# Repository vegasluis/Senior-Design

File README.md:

# Senior-Design

# Problem Identified
Pedestrian fatality rate is three times higher at night. Per the Traffic Safety Facts
(2012 Data), 70% of the pedestrians are killed in the nighttime (6PM – 5:59AM).
A driver can only avoid an accident if he/she sees the pedestrian relatively far
ahead. Headlights only let the driver see about 350 feet ahead.

# Current Solutions
The closest solution in the market is the innovative design Audi has incorporated
to their car model; the Audi A4 is more for personal use rather than a pubic
design. Crosswalk lighting on the street is available to light up sections of the
crosswalk once the light is pressed. Overhead flashing lights, like the Hawk
System, are also used with a set timer to warn drivers that pedestrians are trying
to cross. One tested solution is setting two posts on both sides of the street,
such that once a pedestrian presses a button, the lights turn on to illuminate the
crosswalk.

# Team’s Solution
The Pedestrian Lighting Guidance System is a more efficient way to solve
pedestrian fatalities due to poor visibility at night. The system will be very userfriendly. Pedestrians would not have to do anything different than they usually
do when crossing the street at night, because the pedestrian detection software
will control the spotlight whenever someone triggers it. The system will run
autonomously. The main detail of the
PLGS is its ability to view any object
crossing in the intersection using the
OpenCV libraries. The cameras process
the incoming images and relay the
position to the microprocessors that
control the motor servos, which rotate
180 degrees and will be able to move
the focused spotlights from one side of
the crosswalk to the other. The device
we are trying to create is optimized
more for industrial use, not for
consumer use. It does not require any
sort of reconstruction or modification
on the road.

# Youtube URL

https://www.youtube.com/watch?v=EUFnc7yAI7A

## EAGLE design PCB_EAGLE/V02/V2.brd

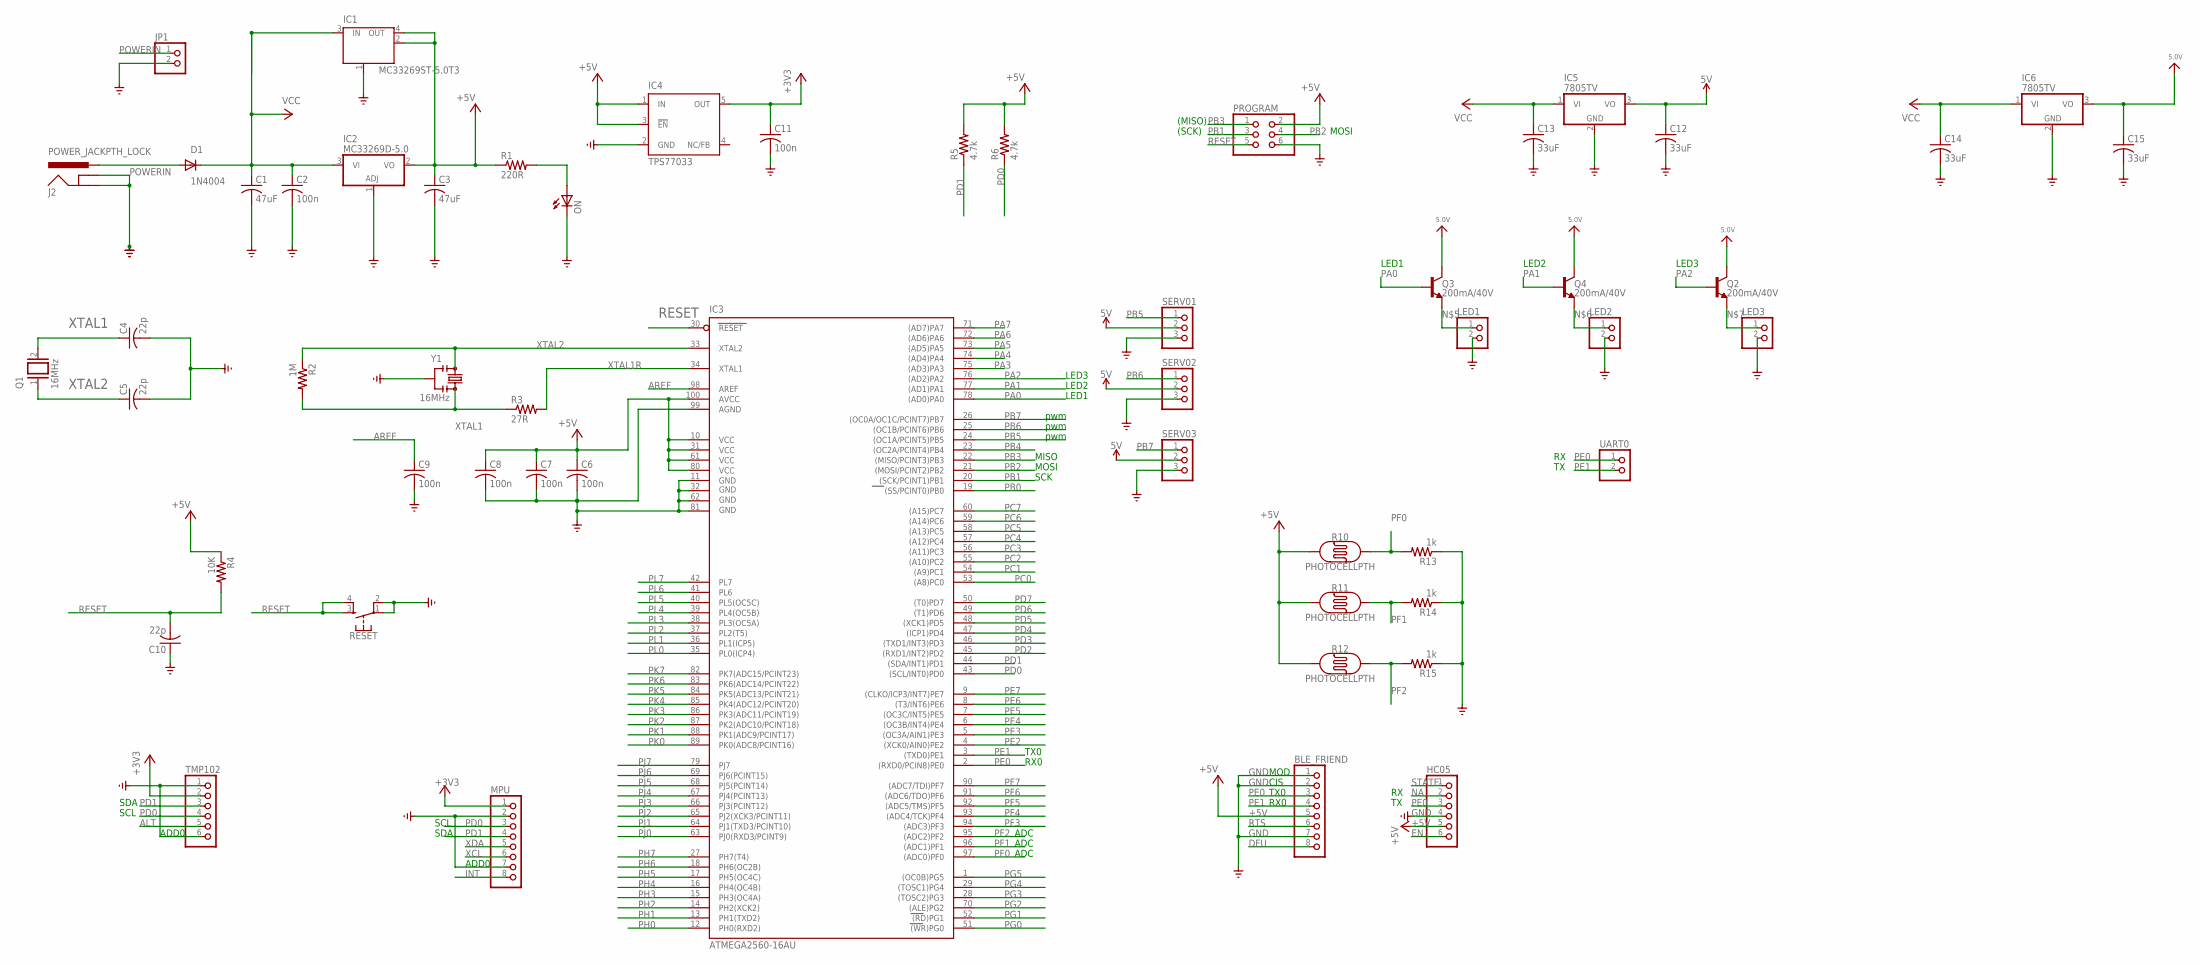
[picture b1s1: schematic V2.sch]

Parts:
BLE_FRIEND: PINHD-1X8; 1X08
C1, C3: 47uF; C025-024X044
C2, C6, C7, C8, C9, C11: 100n; C025-024X044
C4, C5, C10: 22p; C025-024X044
C12, C13, C14, C15: 33uF; C025-024X044
D1: 1N4004; DO41-10
HC05: PINHD-1X6; 1X06
IC1: MC33269ST-5.0T3; SOT223
IC2: MC33269D-5.0; DPACK
IC3: ATMEGA2560-16AU; TQFP100
IC4: TPS77033; SOT23-DBV
IC5, IC6: 7805TV; TO220V
J2: POWER_JACKPTH_LOCK; POWER_JACK_PTH_LOCK
JP1: PINHD-1X2; 1X02
LED1, LED2, LED3: PINHD-1X2; 1X02
MPU: PINHD-1X8; 1X08
ON: LED3MM
PROGRAM: PINHD-2X3; 2X03
Q1: 16MHz; QS
Q2, Q3, Q4: 200mA/40V; TO-92
R1: 220R; 0204V
R2: 1M; 0204V
R3: 27R; 0204V
R4: 10K; 0204V
R5, R6: 4.7k; 0204V
R10, R11, R12: PHOTOCELLPTH; PHOTOCELL
R13, R14, R15: 1k; 0204V
RESET: MOMENTARY-SWITCH-SPST-2-SMD-5.2MM; TACTILE_SWITCH_SMD_5.2MM
SERV01, SERV02, SERV03: PINHD-1X3; 1X03
TMP102: PINHD-1X6; 1X06
UART0: PINHD-1X2; 1X02
Y1: 16MHz; RESONATOR-SMD-3.2X1.3

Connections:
5.0V: C15.1, IC6.3 (VO), Q2.3 (C), Q3.3 (C), Q4.3 (C)
5V: C12.1, IC5.3 (VO), SERV01.2, SERV02.2, SERV03.2
+3V3: C11.1, IC4.5 (OUT), MPU.1, TMP102.2
+5V: BLE_FRIEND.5, C3.1, C6.1, C7.1, C8.1, HC05.5, IC1.2 (OUT), IC1.4 (OUT), IC2.2 (VO), IC3.10 (VCC), IC3.31 (VCC1), IC3.61 (VCC2), IC3.80 (VCC3), IC3.100 (AVCC), IC4.1 (IN), IC4.3 (!EN), PROGRAM.2, R1.1, R4.1, R5.2, R6.2, R10.1, R11.1, R12.1
ALT: TMP102.5
AREF: C9.1, IC3.98 (AREF)
DFU: BLE_FRIEND.8
EN: HC05.6
GND: BLE_FRIEND.1, BLE_FRIEND.2, BLE_FRIEND.7, C1.2, C2.2, C3.2, C4.2, C5.2, C6.2, C7.2, C8.2, C9.2, C10.1, C11.2, C12.2, C13.2, C14.2, C15.2, HC05.4, IC1.1 (GND/ADJ), IC2.1 (ADJ), IC3.11 (GND), IC3.32 (GND1), IC3.62 (GND2), IC3.81 (GND3), IC3.99 (AGND), IC4.2 (GND), IC5.2 (GND), IC6.2 (GND), J2.GND, J2.GNDBREAK, JP1.2, LED1.2, LED2.2, LED3.2, MPU.2, MPU.7, ON.K (C), PROGRAM.6, R13.1, R14.1, R15.1, RESET.1, RESET.2, SERV01.3, SERV02.3, SERV03.3, TMP102.1, TMP102.6, Y1.2
INT: MPU.8
unnamed: ON.A, R1.2
unnamed: LED1.1, Q3.1 (E)
unnamed: LED2.1, Q4.1 (E)
unnamed: LED3.1, Q2.1 (E)
NA: HC05.2
PA0: IC3.78 ((AD0)PA0), Q3.2 (B)
PA1: IC3.77 ((AD1)PA1), Q4.2 (B)
PA2: IC3.76 ((AD2)PA2), Q2.2 (B)
PA3: IC3.75 ((AD3)PA3)
PA4: IC3.74 ((AD4)PA4)
PA5: IC3.73 ((AD5)PA5)
PA6: IC3.72 ((AD6)PA6)
PA7: IC3.71 ((AD7)PA7)
PB0: IC3.19 ((SS/PCINT0)PB0)
PB1: IC3.20 ((SCK/PCINT1)PB1), PROGRAM.3
PB2: IC3.21 ((MOSI/PCINT2)PB2), PROGRAM.4
PB3: IC3.22 ((MISO/PCINT3)PB3), PROGRAM.1
PB4: IC3.23 ((OC2A/PCINT4)PB4)
PB5: IC3.24 ((OC1A/PCINT5)PB5), SERV01.1
PB6: IC3.25 ((OC1B/PCINT6)PB6), SERV02.1
PB7: IC3.26 ((OC0A/OC1C/PCINT7)PB7), SERV03.1
PC0: IC3.53 ((A8)PC0)
PC1: IC3.54 ((A9)PC1)
PC2: IC3.55 ((A10)PC2)
PC3: IC3.56 ((A11)PC3)
PC4: IC3.57 ((A12)PC4)
PC5: IC3.58 ((A13)PC5)
PC6: IC3.59 ((A14)PC6)
PC7: IC3.60 ((A15)PC7)
PD0: IC3.43 ((SCL/INT0)PD0), MPU.3, R6.1, TMP102.4
PD1: IC3.44 ((SDA/INT1)PD1), MPU.4, R5.1, TMP102.3
PD2: IC3.45 ((RXD1/INT2)PD2)
PD3: IC3.46 ((TXD1/INT3)PD3)
PD4: IC3.47 ((ICP1)PD4)
PD5: IC3.48 ((XCK1)PD5)
PD6: IC3.49 ((T1)PD6)
PD7: IC3.50 ((T0)PD7)
PE0: BLE_FRIEND.3, HC05.3, IC3.2 ((RXD0/PCIN8)PE0), UART0.1
PE1: BLE_FRIEND.4, IC3.3 ((TXD0)PE1), UART0.2
PE2: IC3.4 ((XCK0/AIN0)PE2)
PE3: IC3.5 ((OC3A/AIN1)PE3)
PE4: IC3.6 ((OC3B/INT4)PE4)
PE5: IC3.7 ((OC3C/INT5)PE5)
PE6: IC3.8 ((T3/INT6)PE6)
PE7: IC3.9 ((CLKO/ICP3/INT7)PE7)
PF0: IC3.97 ((ADC0)PF0), R10.2, R13.2
PF1: IC3.96 ((ADC1)PF1), R11.2, R14.2
PF2: IC3.95 ((ADC2)PF2), R12.2, R15.2
PF3: IC3.94 ((ADC3)PF3)
PF4: IC3.93 ((ADC4/TCK)PF4)
PF5: IC3.92 ((ADC5/TMS)PF5)
PF6: IC3.91 ((ADC6/TDO)PF6)
PF7: IC3.90 ((ADC7/TDI)PF7)
PG0: IC3.51 ((WR)PG0)
PG1: IC3.52 ((RD)PG1)
PG2: IC3.70 ((ALE)PG2)
PG3: IC3.28 ((TOSC2)PG3)
PG4: IC3.29 ((TOSC1)PG4)
PG5: IC3.1 ((OC0B)PG5)
PH0: IC3.12 (PH0(RXD2))
PH1: IC3.13 (PH1(TXD2))
PH2: IC3.14 (PH2(XCK2))
PH3: IC3.15 (PH3(OC4A))
PH4: IC3.16 (PH4(OC4B))
PH5: IC3.17 (PH5(OC4C))
PH6: IC3.18 (PH6(OC2B))
PH7: IC3.27 (PH7(T4))
PJ0: IC3.63 (PJ0(RXD3/PCINT9))
PJ1: IC3.64 (PJ1(TXD3/PCINT10))
PJ2: IC3.65 (PJ2(XCK3/PCINT11))
PJ3: IC3.66 (PJ3(PCINT12))
PJ4: IC3.67 (PJ4(PCINT13))
PJ5: IC3.68 (PJ5(PCINT14))
PJ6: IC3.69 (PJ6(PCINT15))
PJ7: IC3.79 (PJ7)
PK0: IC3.89 (PK0(ADC8/PCINT16))
PK1: IC3.88 (PK1(ADC9/PCINT17))
PK2: IC3.87 (PK2(ADC10/PCINT18))
PK3: IC3.86 (PK3(ADC11/PCINT19))
PK4: IC3.85 (PK4(ADC12/PCINT20))
PK5: IC3.84 (PK5(ADC13/PCINT21))
PK6: IC3.83 (PK6(ADC14/PCINT22))
PK7: IC3.82 (PK7(ADC15/PCINT23))
PL0: IC3.35 (PL0(ICP4))
PL1: IC3.36 (PL1(ICP5))
PL2: IC3.37 (PL2(T5))
PL3: IC3.38 (PL3(OC5A))
PL4: IC3.39 (PL4(OC5B))
PL5: IC3.40 (PL5(OC5C))
PL6: IC3.41 (PL6)
PL7: IC3.42 (PL7)
POWERIN: D1.A, J2.PWR, JP1.1
RESET: C10.2, IC3.30 (RESET), PROGRAM.5, R4.2, RESET.3, RESET.4
RTS: BLE_FRIEND.6
STATE: HC05.1
VCC: C1.1, C2.1, C13.1, C14.1, D1.C, IC1.3 (IN), IC2.3 (VI), IC5.1 (VI), IC6.1 (VI)
XCL: MPU.6
XDA: MPU.5
XTAL1: C4.1, Q1.2, R2.2, R3.1, Y1.3
XTAL1R: IC3.34 (XTAL1), R3.2
XTAL2: C5.1, IC3.33 (XTAL2), Q1.1, R2.1, Y1.1

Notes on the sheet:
pwm
ADD0
ADC
(MISO)
(SCK)
MOSI
MISO
SCK
TX0
RX0
SDA
SCL
MOD
CIS
LED1
LED2
LED3

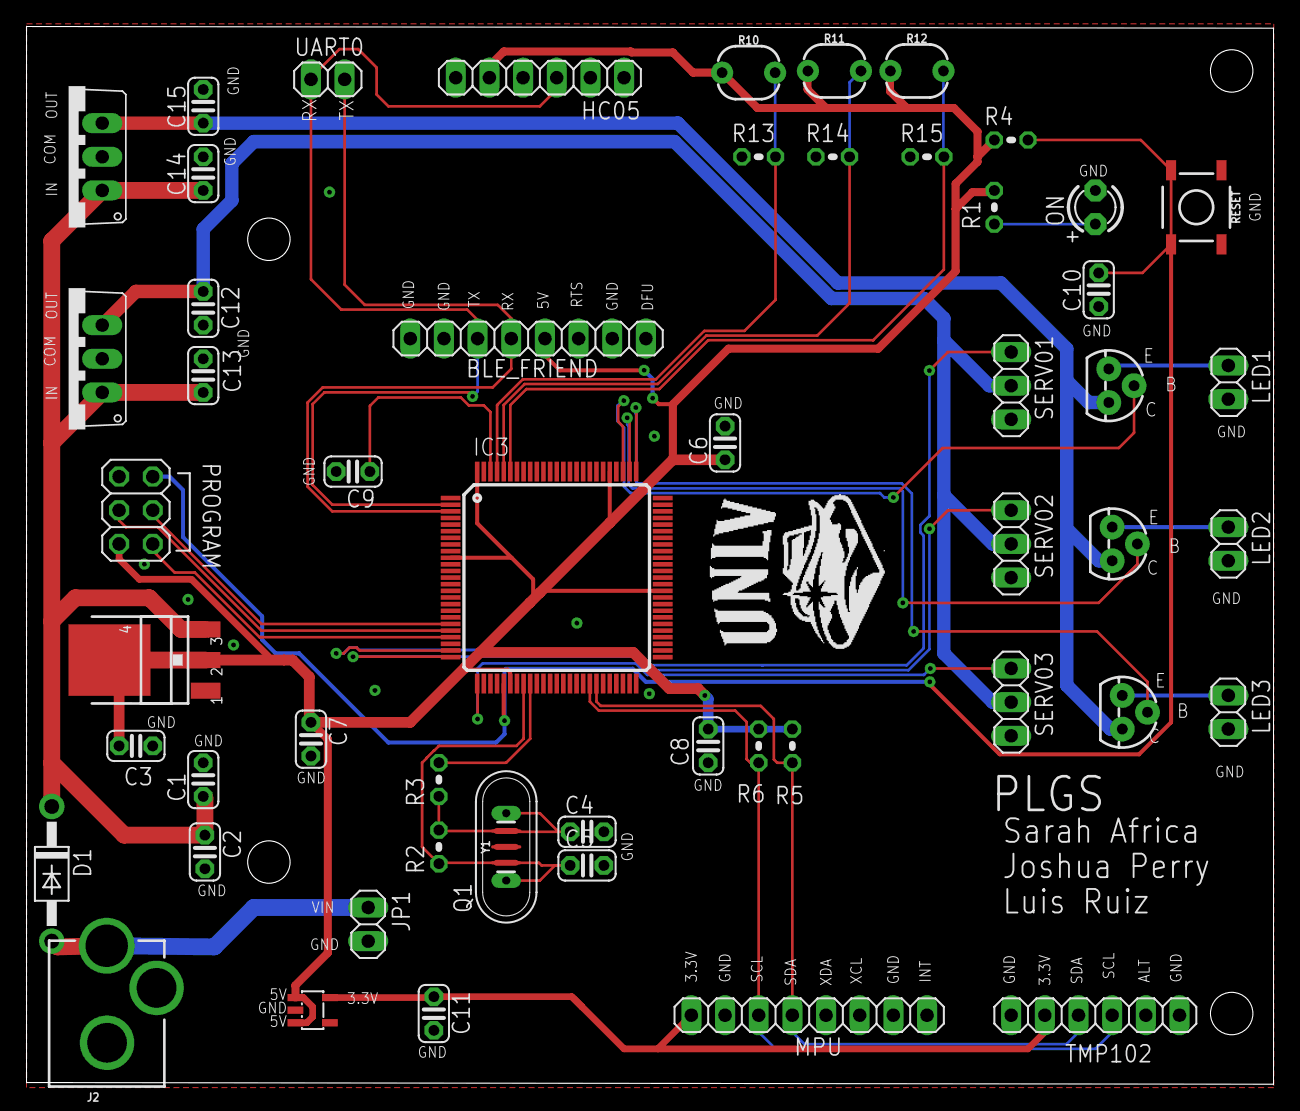
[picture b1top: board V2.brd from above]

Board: 2 copper layers, 94.1 x 79.8 mm, 55 parts (0 on the bottom side), 32 nets.

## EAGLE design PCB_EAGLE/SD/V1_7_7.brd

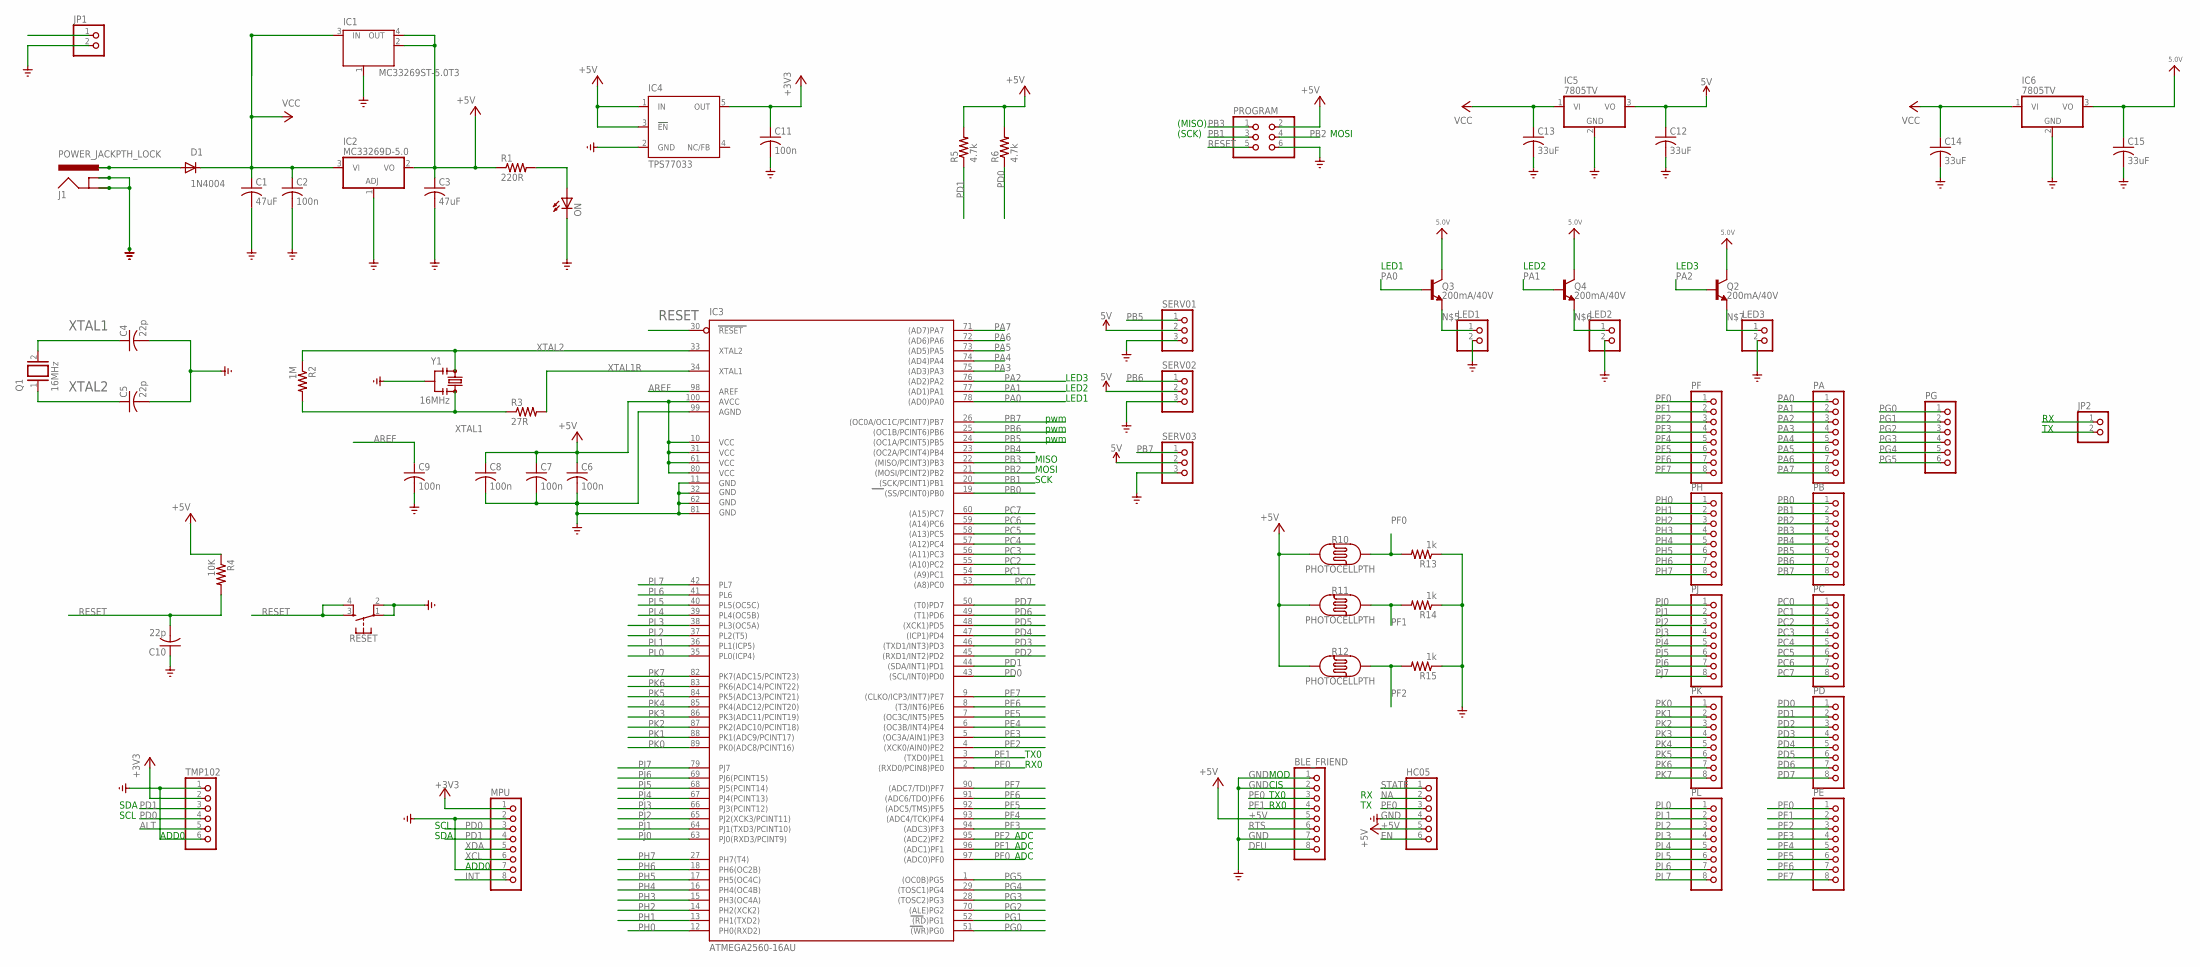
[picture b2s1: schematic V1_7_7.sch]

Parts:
BLE_FRIEND: PINHD-1X8; 1X08
C1, C3: 47uF; C025-024X044
C2, C6, C7, C8, C9, C11: 100n; C025-024X044
C4, C5, C10: 22p; C025-024X044
C12, C13, C14, C15: 33uF; C025-024X044
D1: 1N4004; DO41-10
HC05: PINHD-1X6; 1X06
IC1: MC33269ST-5.0T3; SOT223
IC2: MC33269D-5.0; DPACK
IC3: ATMEGA2560-16AU; TQFP100
IC4: TPS77033; SOT23-DBV
IC5, IC6: 7805TV; TO220V
J1: POWER_JACKPTH_LOCK; POWER_JACK_PTH_LOCK
JP1, JP2: PINHD-1X2; 1X02
LED1, LED2, LED3: PINHD-1X2; 1X02
MPU: PINHD-1X8; 1X08
ON: LED3MM
PA: PINHD-1X8; 1X08
PB: PINHD-1X8; 1X08
PC: PINHD-1X8; 1X08
PD: PINHD-1X8; 1X08
PE: PINHD-1X8; 1X08
PF: PINHD-1X8; 1X08
PG: PINHD-1X6; 1X06
PH: PINHD-1X8; 1X08
PJ: PINHD-1X8; 1X08
PK: PINHD-1X8; 1X08
PL: PINHD-1X8; 1X08
PROGRAM: PINHD-2X3; 2X03
Q1: 16MHz; QS
Q2, Q3, Q4: 200mA/40V; TO-92
R1: 220R; 0204V
R2: 1M; 0204V
R3: 27R; 0204V
R4: 10K; 0204V
R5, R6: 4.7k; 0204V
R10, R11, R12: PHOTOCELLPTH; PHOTOCELL
R13, R14, R15: 1k; 0204V
RESET: MOMENTARY-SWITCH-SPST-2-SMD-5.2MM; TACTILE_SWITCH_SMD_5.2MM
SERV01, SERV02, SERV03: PINHD-1X3; 1X03
TMP102: PINHD-1X6; 1X06
Y1: 16MHz; RESONATOR-SMD-3.2X1.3

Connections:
5.0V: C15.1, IC6.3 (VO), Q2.3 (C), Q3.3 (C), Q4.3 (C)
5V: C12.1, IC5.3 (VO), SERV01.2, SERV02.2, SERV03.2
+3V3: C11.1, IC4.5 (OUT), MPU.1, TMP102.2
+5V: BLE_FRIEND.5, C3.1, C6.1, C7.1, C8.1, HC05.5, IC1.2 (OUT), IC1.4 (OUT), IC2.2 (VO), IC3.10 (VCC), IC3.31 (VCC1), IC3.61 (VCC2), IC3.80 (VCC3), IC3.100 (AVCC), IC4.1 (IN), IC4.3 (!EN), PROGRAM.2, R1.1, R4.1, R5.2, R6.2, R10.1, R11.1, R12.1
ALT: TMP102.5
AREF: C9.1, IC3.98 (AREF)
DFU: BLE_FRIEND.8
EN: HC05.6
GND: BLE_FRIEND.1, BLE_FRIEND.2, BLE_FRIEND.7, C1.2, C2.2, C3.2, C4.2, C5.2, C6.2, C7.2, C8.2, C9.2, C10.1, C11.2, C12.2, C13.2, C14.2, C15.2, HC05.4, IC1.1 (GND/ADJ), IC2.1 (ADJ), IC3.11 (GND), IC3.32 (GND1), IC3.62 (GND2), IC3.81 (GND3), IC3.99 (AGND), IC4.2 (GND), IC5.2 (GND), IC6.2 (GND), J1.GND, J1.GNDBREAK, JP1.2, LED1.2, LED2.2, LED3.2, MPU.2, MPU.7, ON.K (C), PROGRAM.6, R13.1, R14.1, R15.1, RESET.1, RESET.2, SERV01.3, SERV02.3, SERV03.3, TMP102.1, TMP102.6, Y1.2
INT: MPU.8
unnamed: ON.A, R1.2
unnamed: LED1.1, Q3.1 (E)
unnamed: LED2.1, Q4.1 (E)
unnamed: LED3.1, Q2.1 (E)
NA: HC05.2
PA0: IC3.78 ((AD0)PA0), PA.1, Q3.2 (B)
PA1: IC3.77 ((AD1)PA1), PA.2, Q4.2 (B)
PA2: IC3.76 ((AD2)PA2), PA.3, Q2.2 (B)
PA3: IC3.75 ((AD3)PA3), PA.4
PA4: IC3.74 ((AD4)PA4), PA.5
PA5: IC3.73 ((AD5)PA5), PA.6
PA6: IC3.72 ((AD6)PA6), PA.7
PA7: IC3.71 ((AD7)PA7), PA.8
PB0: IC3.19 ((SS/PCINT0)PB0), PB.1
PB1: IC3.20 ((SCK/PCINT1)PB1), PB.2, PROGRAM.3
PB2: IC3.21 ((MOSI/PCINT2)PB2), PB.3, PROGRAM.4
PB3: IC3.22 ((MISO/PCINT3)PB3), PB.4, PROGRAM.1
PB4: IC3.23 ((OC2A/PCINT4)PB4), PB.5
PB5: IC3.24 ((OC1A/PCINT5)PB5), PB.6, SERV01.1
PB6: IC3.25 ((OC1B/PCINT6)PB6), PB.7, SERV02.1
PB7: IC3.26 ((OC0A/OC1C/PCINT7)PB7), PB.8, SERV03.1
PC0: IC3.53 ((A8)PC0), PC.1
PC1: IC3.54 ((A9)PC1), PC.2
PC2: IC3.55 ((A10)PC2), PC.3
PC3: IC3.56 ((A11)PC3), PC.4
PC4: IC3.57 ((A12)PC4), PC.5
PC5: IC3.58 ((A13)PC5), PC.6
PC6: IC3.59 ((A14)PC6), PC.7
PC7: IC3.60 ((A15)PC7), PC.8
PD0: IC3.43 ((SCL/INT0)PD0), MPU.3, PD.1, R6.1, TMP102.4
PD1: IC3.44 ((SDA/INT1)PD1), MPU.4, PD.2, R5.1, TMP102.3
PD2: IC3.45 ((RXD1/INT2)PD2), PD.3
PD3: IC3.46 ((TXD1/INT3)PD3), PD.4
PD4: IC3.47 ((ICP1)PD4), PD.5
PD5: IC3.48 ((XCK1)PD5), PD.6
PD6: IC3.49 ((T1)PD6), PD.7
PD7: IC3.50 ((T0)PD7), PD.8
PE0: BLE_FRIEND.3, HC05.3, IC3.2 ((RXD0/PCIN8)PE0), JP2.1, PE.1
PE1: BLE_FRIEND.4, IC3.3 ((TXD0)PE1), JP2.2, PE.2
PE2: IC3.4 ((XCK0/AIN0)PE2), PE.3
PE3: IC3.5 ((OC3A/AIN1)PE3), PE.4
PE4: IC3.6 ((OC3B/INT4)PE4), PE.5
PE5: IC3.7 ((OC3C/INT5)PE5), PE.6
PE6: IC3.8 ((T3/INT6)PE6), PE.7
PE7: IC3.9 ((CLKO/ICP3/INT7)PE7), PE.8
PF0: IC3.97 ((ADC0)PF0), PF.1, R10.2, R13.2
PF1: IC3.96 ((ADC1)PF1), PF.2, R11.2, R14.2
PF2: IC3.95 ((ADC2)PF2), PF.3, R12.2, R15.2
PF3: IC3.94 ((ADC3)PF3), PF.4
PF4: IC3.93 ((ADC4/TCK)PF4), PF.5
PF5: IC3.92 ((ADC5/TMS)PF5), PF.6
PF6: IC3.91 ((ADC6/TDO)PF6), PF.7
PF7: IC3.90 ((ADC7/TDI)PF7), PF.8
PG0: IC3.51 ((WR)PG0), PG.1
PG1: IC3.52 ((RD)PG1), PG.2
PG2: IC3.70 ((ALE)PG2), PG.3
PG3: IC3.28 ((TOSC2)PG3), PG.4
PG4: IC3.29 ((TOSC1)PG4), PG.5
PG5: IC3.1 ((OC0B)PG5), PG.6
PH0: IC3.12 (PH0(RXD2)), PH.1
PH1: IC3.13 (PH1(TXD2)), PH.2
PH2: IC3.14 (PH2(XCK2)), PH.3
PH3: IC3.15 (PH3(OC4A)), PH.4
PH4: IC3.16 (PH4(OC4B)), PH.5
PH5: IC3.17 (PH5(OC4C)), PH.6
PH6: IC3.18 (PH6(OC2B)), PH.7
PH7: IC3.27 (PH7(T4)), PH.8
PJ0: IC3.63 (PJ0(RXD3/PCINT9)), PJ.1
PJ1: IC3.64 (PJ1(TXD3/PCINT10)), PJ.2
PJ2: IC3.65 (PJ2(XCK3/PCINT11)), PJ.3
PJ3: IC3.66 (PJ3(PCINT12)), PJ.4
PJ4: IC3.67 (PJ4(PCINT13)), PJ.5
PJ5: IC3.68 (PJ5(PCINT14)), PJ.6
PJ6: IC3.69 (PJ6(PCINT15)), PJ.7
PJ7: IC3.79 (PJ7), PJ.8
PK0: IC3.89 (PK0(ADC8/PCINT16)), PK.1
PK1: IC3.88 (PK1(ADC9/PCINT17)), PK.2
PK2: IC3.87 (PK2(ADC10/PCINT18)), PK.3
PK3: IC3.86 (PK3(ADC11/PCINT19)), PK.4
PK4: IC3.85 (PK4(ADC12/PCINT20)), PK.5
PK5: IC3.84 (PK5(ADC13/PCINT21)), PK.6
PK6: IC3.83 (PK6(ADC14/PCINT22)), PK.7
PK7: IC3.82 (PK7(ADC15/PCINT23)), PK.8
PL0: IC3.35 (PL0(ICP4)), PL.1
PL1: IC3.36 (PL1(ICP5)), PL.2
PL2: IC3.37 (PL2(T5)), PL.3
PL3: IC3.38 (PL3(OC5A)), PL.4
PL4: IC3.39 (PL4(OC5B)), PL.5
PL5: IC3.40 (PL5(OC5C)), PL.6
PL6: IC3.41 (PL6), PL.7
PL7: IC3.42 (PL7), PL.8
POWERIN: D1.A, J1.PWR, JP1.1
RESET: C10.2, IC3.30 (RESET), PROGRAM.5, R4.2, RESET.3, RESET.4
RTS: BLE_FRIEND.6
STATE: HC05.1
VCC: C1.1, C2.1, C13.1, C14.1, D1.C, IC1.3 (IN), IC2.3 (VI), IC5.1 (VI), IC6.1 (VI)
XCL: MPU.6
XDA: MPU.5
XTAL1: C4.1, Q1.2, R2.2, R3.1, Y1.3
XTAL1R: IC3.34 (XTAL1), R3.2
XTAL2: C5.1, IC3.33 (XTAL2), Q1.1, R2.1, Y1.1

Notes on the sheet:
pwm
ADD0
ADC
(MISO)
(SCK)
MOSI
MISO
SCK
TX0
RX0
SDA
SCL
MOD
CIS
LED1
LED2
LED3

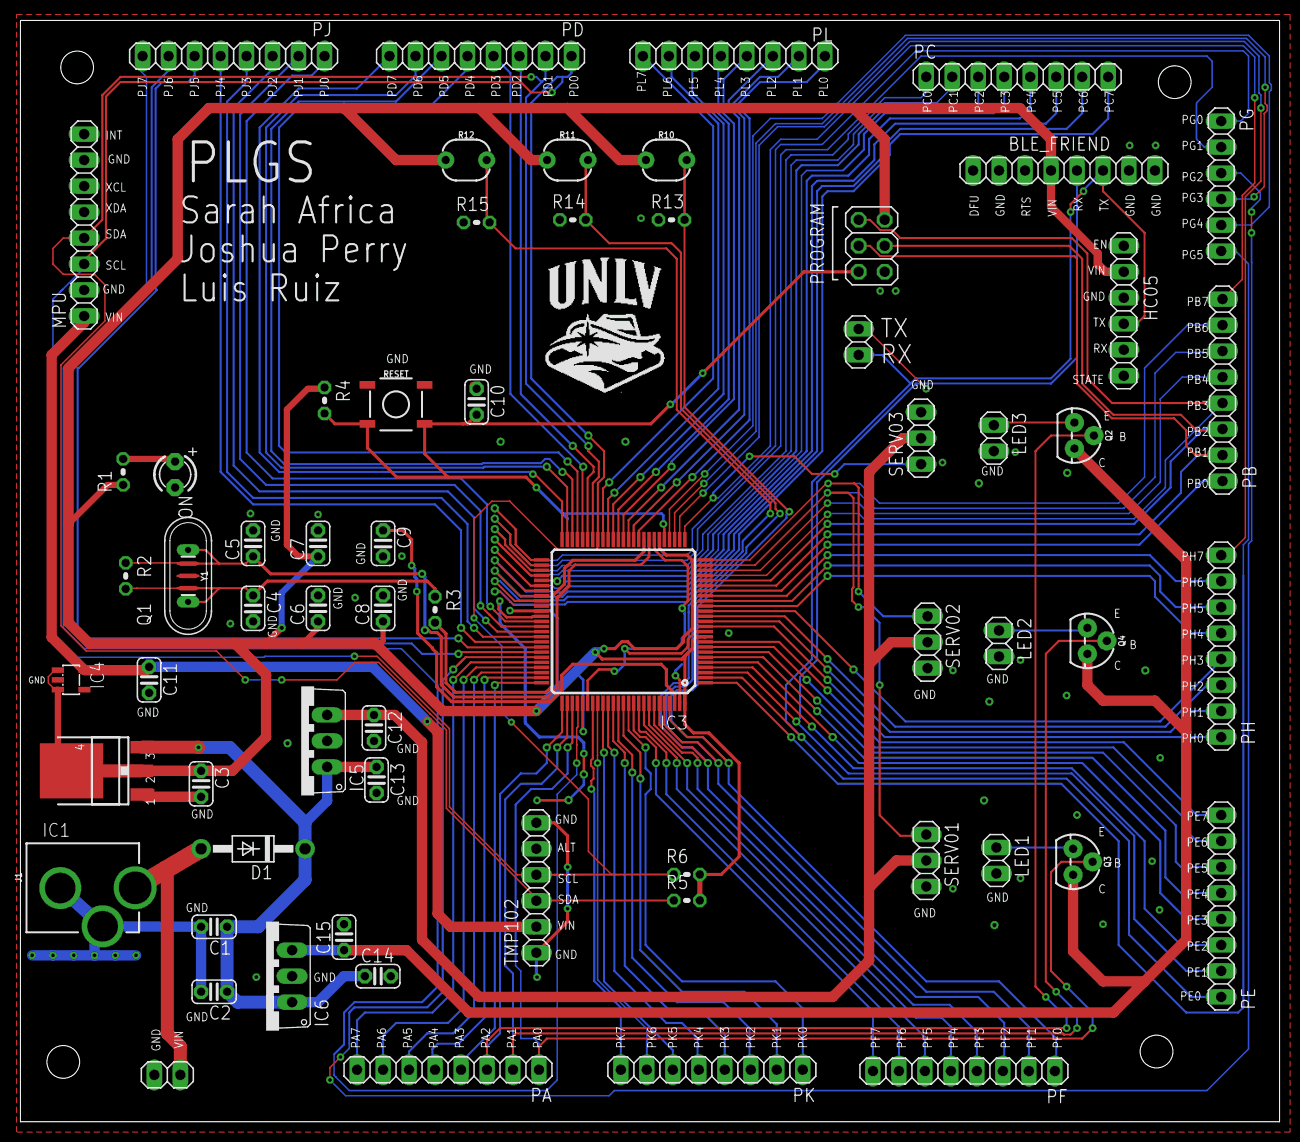
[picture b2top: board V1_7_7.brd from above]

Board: 2 copper layers, 123.0 x 107.6 mm, 66 parts (0 on the bottom side), 102 nets.

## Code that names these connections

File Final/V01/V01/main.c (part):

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	switch(servoNum){
		case '1': 
		{
			if(on == '1') PORTA |= (1<<PA0);
			else PORTA &= ~(1<<PA0);
			break;
		}
		case '2':
		{
			if(on == '1') PORTA |= (1<<PA1);
			else PORTA &= ~(1<<PA1);
			break;
		}
		case '3':
		{
			if(on == '1') PORTA |= (1<<PA2);
			else PORTA &= ~(1<<PA2);
			break;
		}
		default:printm_0("Servo Number does not exist\r\n");break;
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	if(accelX >= 15 || accelX <= -15 || accelY >= 15 ||
		accelY <= -15 || accelZ >= 15 || accelZ <= -15)
	{
		PORTA |= (1<<PA0)|(1<<PA1)|(1<<PA2);
		/*
		 * Angles set later 
		 */
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
	//LED
	//set as outputs
	DDRA |= (1<<PA0)|(1<<PA1)|(1<<PA2);

	//**************************************************
	//I2C
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	i2c_init();

	//Set SCL and SDA as in Inputs
	DDRD &= (0<<PD0)|(0<<PD1); 

	//Pull UP 
	PORTD |= (1<<PD0)|(1<<PD1); 
	
	//**************************************************
	//MPU6050
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{
	for(int i = 20; i < 20; ++i)
	{
		PORTA |= (1<<PA0);
		PORTA &= (0<<PA1)&(0<<PA2);
		_delay_ms(100);
		PORTA |= (1<<PA1);
		PORTA &= (0<<PA0)&(0<<PA2);
		_delay_ms(100);
		PORTA |= (1<<PA2);
		PORTA &= (0<<PA1)&(0<<PA0);
		_delay_ms(100);
	}
	PORTA &= (0<<PA0)|(0<<PA1)|(0<<PA2);
}


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
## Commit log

2017-09-30 9/29/17
2017-10-22 10/22/17
2018-01-11 I2C part was removed
2018-01-11 eagle files

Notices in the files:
parts and their libraries:
SparkFun-Connectors: Licensing: Creative Commons ShareAlike 4.0 International - https://creativecommons.org/licenses/by-sa/4.0
supply0: Copyright (C) 2007, Bob Starr
